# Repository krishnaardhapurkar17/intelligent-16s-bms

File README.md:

# Simulation-First 16S Intelligent BMS

A simulation-first 16-series-cell Intelligent Battery Management System.

## Development Stack
- Python
- PyBaMM
- NumPy / SciPy
- Pandas
- Matplotlib
- Pytest
- KiCad

## Project Scope
- 16S battery modelling
- Cell monitoring
- SOC/SOH/SOP/SOS estimation
- Fault detection and localization
- Active balancing simulation
- AI-based battery diagnostics
- CMU/BMU/PMU/BDU architecture
- Verification and validation

## Project Status
Simulation models, diagnostics, supervisory controls, PMU/IMU/TMU abstractions,
and BDU protection logic are present. Transport-independent message contracts,
simulation command authorization, and lifecycle event logging/replay are also
implemented. See `docs/requirements-traceability-matrix.md` for verified gaps;
the RTM is an engineering worklist, not a certification statement.
The [75-task evidence-based tracker reconciliation](outputs/01a1c0ed-8d57-7813-b837-d1bb78c2df39/project_tracker_reconciliation.xlsx)
is the detailed cross-project status view. The two supplied project-tracker
workbooks also now contain current status/evidence fields; their original task
statuses are retained in a baseline column. The GOV-003 workbook preserves its
original audit sheets and includes a dated current-scope addendum. The V&V,
execution, and risk Word plans have dated status addenda; their original
baseline content remains in place.

The hardware files are a non-release schematic/design study. Grounded USB
service is prohibited while the pack is connected; the active-balancer is
deferred from the build/procurement baseline; external high-voltage switching
components remain unselected; and physical IMD/HVIL, PCB layout and physical
validation are outside the current scope. Do not connect a battery to the
draft design.

Reproducible idealized precharge R-C, software fault-injection, and synthetic dynamic-load SOC
initialization experiments are included. They are software-model evidence,
not KiCad SPICE, component-model, hardware, or vehicle validation. See
`docs/portfolio-evidence-register.md`.

## Supplied AI estimators

Supplied NMC/NMC-LCO model assets are preserved under `models/ai/`. Portable
LFP SOH/RUL forests trained on UConn reference performance tests are also
available through the AI adapter; their whole-cell held-out results and limits
are documented in `models/ai/README.md`. LFP SOC AI remains disabled because
the available data do not support independent cell-held-out validation of a
temperature-aware model. All AI estimates are research-only warnings and must
not replace primary protection logic. See `models/ai/README.md` for feature
contracts and verification evidence.

## Run checks
Create an isolated environment and install the core project dependencies:

```powershell
py -m venv .venv
.\.venv\Scripts\python.exe -m pip install -r environment/requirements-core.txt
```

For SOC CNN-LSTM inference, also install
`.\.venv\Scripts\python.exe -m pip install -r environment/requirements-ai.txt`.
Run the regression suite with
`.\.venv\Scripts\python.exe tests/regression/run_regression.py`. It writes its
report under `results/regression/`.

Regenerate the focused assumption-only experiments with:

```powershell
.\.venv\Scripts\python.exe tools\run_precharge_assumption_sim.py
.\.venv\Scripts\python.exe tools\run_soc_drive_cycle_experiment.py
.\.venv\Scripts\python.exe tools\run_software_fault_injection_report.py
```

## LFP model data workflow

Keep the downloaded raw files in `datasets/` (they are excluded from Git). Run
`.\.venv\Scripts\python.exe tools/prepare_lfp_dataset.py --all` to build compact
tables under `results/raw/lfp/`, then run
`.\.venv\Scripts\python.exe tools/train_lfp_tree_models.py` to train LFP SOH/RUL
forests and reproduce the whole-cell validation report. Add
`--split protocol-group` to evaluate on unseen aging conditions. See
`models/ai/README.md` for metrics, limits, and the disabled LFP SOC AI path.

For the complete unit suite, run
`.\.venv\Scripts\python.exe -m pytest tests/unit -q`. For statement and
branch coverage, install `environment/requirements-dev.txt`, run
`coverage run --branch --source=software,models -m pytest tests/unit -q`, then
`coverage report -m`. The current result is recorded in
`results/metrics/unit_test_coverage.json`; coverage is not a safety metric.

## Limitations
Simulation and engineering design project.
Not safety certified or production qualified.

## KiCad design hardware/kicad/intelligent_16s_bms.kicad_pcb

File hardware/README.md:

# Hardware workspace

The hardware design is a control-board schematic draft. Pack current remains
off-board through external contactors, fuse, shunt and precharge components.
No board is being fabricated or physically tested.

## Integrated CAD

- [Integrated KiCad schematic](kicad/intelligent_16s_bms.kicad_sch)
- [Integrated schematic PDF](schematic-pdf/intelligent_16s_bms_system.pdf)
- [Integrated ERC report](kicad/integrated_erc.txt)
- [Integrated netlist](kicad/intelligent_16s_bms.net)
- [Draft BOM](bom/intelligent_16s_bms_draft.csv)
- [BOM authority and status](bom/README.md)
- [Design checklist](requirements-status.md)
- [Circuit definition and release gates](circuit-definition.md)

The source-page generators are in `tools/generate_afe_schematic.py`,
`tools/generate_controller_schematic.py`, `tools/generate_power_schematic.py`
and `tools/generate_balancer_schematic.py`. Recreate the project entry sheet
with `tools/merge_hardware_schematic.py` after regenerating the child sheets.
The root schematic is intentionally a single project sheet with separate child
sheets for AFE, controller, power/auxiliary logic and active balancing, instead
of one giant flat capture. The root plus four child sheets make a five-page
project. The sheets use global labels for cross-sheet nets and distinct
reference ranges for the controller, auxiliary-power and active-balancer pages.

From the repository root, regenerate the design and project-local symbol
library with:

```powershell
python .\tools\generate_afe_schematic.py
python .\tools\generate_controller_schematic.py
python .\tools\generate_power_schematic.py
python .\tools\generate_balancer_schematic.py
python .\tools\merge_hardware_schematic.py
python .\tools\export_kicad_custom_library.py
```

KiCad 10.0.6 ERC on the top-level, five-page schematic reports zero errors and
zero warnings with `--severity-all`. The report lists excluded check classes,
including SPICE-model issues. ERC checks schematic rules only; it is not
electrical design approval, circuit simulation, or DRC.

The controller and active-balancer source sheets now include explicit review
warnings. These are annotation-only changes; no connectivity was changed. The
schematic PDF and ERC report are refreshed from the integrated schematic.

## Current scope decisions

- Grounded USB service is prohibited while the pack is connected; no live-pack
  USB isolation redesign is claimed.
- The active-balancer circuit is a study only and is deferred from the
  build/procurement baseline. Do not populate or procure its transformer
  candidate without approval or a reviewed replacement.
- External pack switching, fuse, shunt and precharge hardware remain
  unselected. The physical IMD/HVIL, PCB layout, KiCad SPICE simulation,
  fabrication and all physical testing are outside this revision.
- The package is not a hardware release. Do not connect a battery to this
  unvalidated draft.

The KiCad PCB file contains imported footprints but no routed copper, vias,
zones or DRC evidence. It is an unrouted placement draft, not a completed
layout. Contactor coil settings remain provisional; cell-specific
configuration, external contactor/fuse/precharge selection, physical IMD/HVIL
and independent review remain open if hardware release is later pursued.

The idealized software precharge study is reproducible with
`tools/run_precharge_assumption_sim.py`; it is not a KiCad SPICE run or
component-model validation. KiCad circuit-level simulation remains open and is
intentionally untouched in this revision.

The software state-machine behavior is described in
`docs/bdu-state-machine.md`; project status and limitations are summarized in
`docs/portfolio-evidence-register.md`.

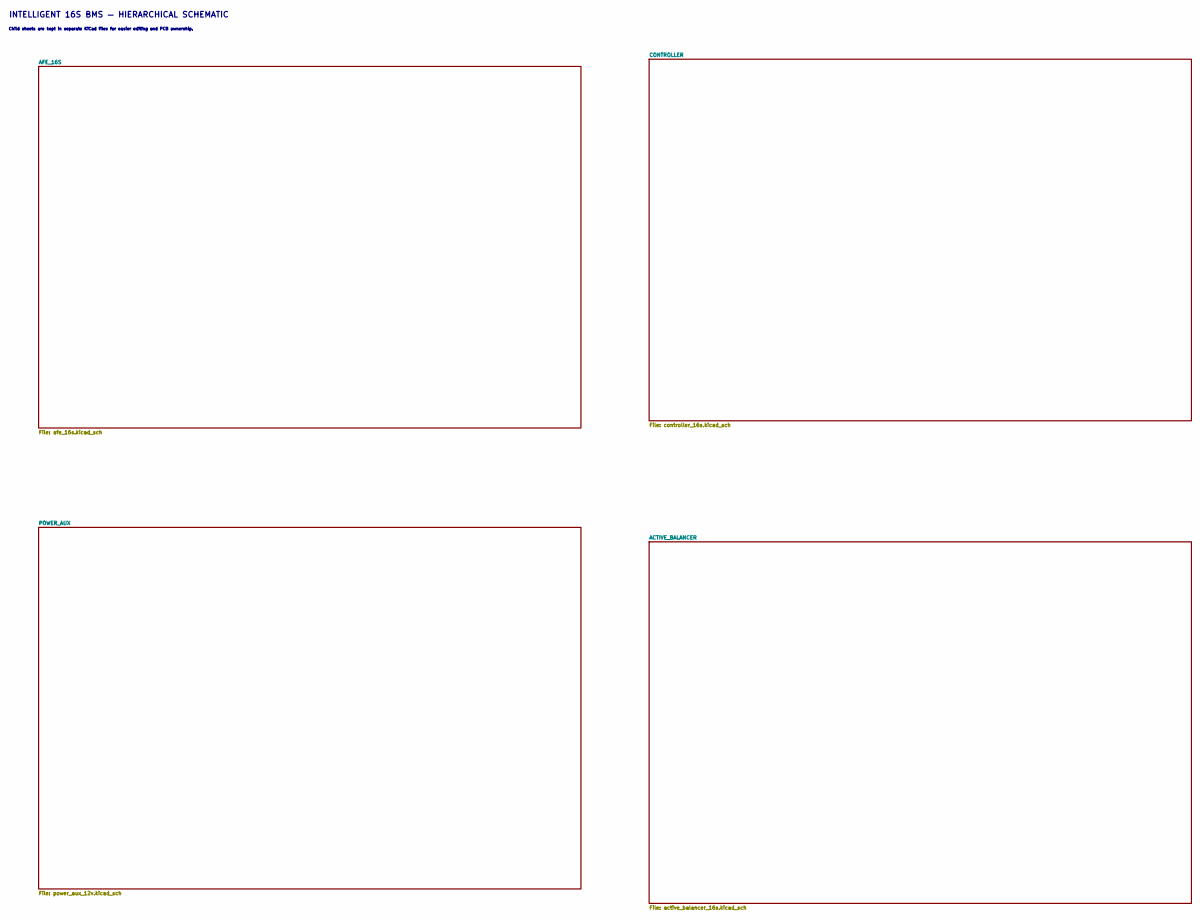
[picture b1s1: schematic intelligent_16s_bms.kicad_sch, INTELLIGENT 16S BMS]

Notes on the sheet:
Child sheets are kept in separate KiCad files for easier editing and PCB ownership.
INTELLIGENT 16S BMS — HIERARCHICAL SCHEMATIC

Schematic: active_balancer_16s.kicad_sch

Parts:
C301, C302, C303, C304, C305, C306, C307, C308, C309, C310, C311, C312, C313, C314, C315, C316: 47uF 16V X7R; Ceff >= 12uF; C_1210_3225Metric
C320, C321, C322: 10uF VREG bulk; C_0805_2012Metric
C330, C332, C334: 100nF isolator bypass; C_0603_1608Metric
C331, C333, C335: 100nF local isolator bypass; C_0603_1608Metric
C336: 100nF boost capacitor; C_0603_1608Metric
D30: Schottky; VRRM>6V, surge>=1A; D_SOD-123
J30: BALANCE POWER TAPS VC0..VC16; 3 spare; Molex_Mini-Fit_Jr_5566-20A_2x10_P4.20mm_Vertical
Q30, Q31, Q32, Q33, Q34, Q35, Q36, Q37, Q38, Q39, Q40, Q41, Q42, Q43, Q44, Q45, Q46, Q47, Q48, Q49, Q50, Q51, Q52, Q53, Q54, Q55, Q56, Q57, Q58, Q59, Q60, Q61: BUK9Y22-100E 100V; LFPAK56
Q62, Q63, Q64: BC857B-Q WDT pause; SOT-23
R301, R303, R305, R307, R309, R311, R313, R315, R317, R319, R321, R323, R325, R327, R329, R331: 25mR 1% primary peak sense; R_2512_6332Metric
R302, R304, R306, R308, R310, R312, R314, R316, R318, R320, R322, R324, R326, R328, R330, R332: 25mR 1% secondary peak sense; R_2512_6332Metric
R340, R342, R344: 20k RTONP; R_0603_1608Metric
R341, R343, R345: 15k RTONS; R_0603_1608Metric
R349: 6.8R boost inrush; R_0603_1608Metric
R350, R351, R352: 10k WDT pull-up; R_0603_1608Metric
R353, R354, R355: 10k SDO pull-up; R_0603_1608Metric
R356, R358, R360: 10k WDT pause drive; R_0603_1608Metric
R357, R359, R361: 100k default inhibit; R_0603_1608Metric
T30, T31, T32, T33, T34, T35, T36, T37, T38, T39, T40, T41, T42, T43, T44, T45: WE-FLYLT 750312504
U30, U31, U32: LTC3300ILXE-2#WPBF; LQFP-48-1EP_7x7mm_P0.5mm_EP3.6x3.6mm
U33, U34, U35: ISO7762F-Q1; SOIC-16W_7.5x10.3mm_P1.27mm

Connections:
3V3: C330.1, C332.1, C334.1, U33.1 (VCC1), U34.1 (VCC1), U35.1 (VCC1); also elsewhere on the board
BAL_BOOST_DIODE_IN: D30.2 (A), R349.1
BAL_BOOST_MINUS_U32: C336.2, U32.41 (BOOST-)
BAL_BOOST_PLUS_U32: C336.1, D30.1 (K), U32.40 (BOOST+)
BAL_CS30: U33.2 (INA); also elsewhere on the board
BAL_CS31: U34.2 (INA); also elsewhere on the board
BAL_CS32: U35.2 (INA); also elsewhere on the board
BAL_CS_LOCAL_U30: U30.16 (CSBI), U33.15 (OUTA)
BAL_CS_LOCAL_U31: U31.16 (CSBI), U34.15 (OUTA)
BAL_CS_LOCAL_U32: U32.16 (CSBI), U35.15 (OUTA)
BAL_G1P_U30: Q30.1 (G), U30.23 (G1P)
BAL_G1P_U31: Q42.1 (G), U31.23 (G1P)
BAL_G1S_U30: Q31.1 (G), U30.11 (G1S)
BAL_G1S_U31: Q43.1 (G), U31.11 (G1S)
BAL_G2P_U30: Q32.1 (G), U30.26 (G2P)
BAL_G2P_U31: Q44.1 (G), U31.26 (G2P)
BAL_G2S_U30: Q33.1 (G), U30.9 (G2S)
BAL_G2S_U31: Q45.1 (G), U31.9 (G2S)
BAL_G3P_U30: Q34.1 (G), U30.29 (G3P)
BAL_G3P_U31: Q46.1 (G), U31.29 (G3P)
BAL_G3P_U32: Q54.1 (G), U32.29 (G3P)
BAL_G3S_U30: Q35.1 (G), U30.7 (G3S)
BAL_G3S_U31: Q47.1 (G), U31.7 (G3S)
BAL_G3S_U32: Q55.1 (G), U32.7 (G3S)
BAL_G4P_U30: Q36.1 (G), U30.32 (G4P)
BAL_G4P_U31: Q48.1 (G), U31.32 (G4P)
BAL_G4P_U32: Q56.1 (G), U32.32 (G4P)
BAL_G4S_U30: Q37.1 (G), U30.5 (G4S)
BAL_G4S_U31: Q49.1 (G), U31.5 (G4S)
BAL_G4S_U32: Q57.1 (G), U32.5 (G4S)
BAL_G5P_U30: Q38.1 (G), U30.35 (G5P)
BAL_G5P_U31: Q50.1 (G), U31.35 (G5P)
BAL_G5P_U32: Q58.1 (G), U32.35 (G5P)
BAL_G5S_U30: Q39.1 (G), U30.3 (G5S)
BAL_G5S_U31: Q51.1 (G), U31.3 (G5S)
BAL_G5S_U32: Q59.1 (G), U32.3 (G5S)
BAL_G6P_U30: Q40.1 (G), U30.38 (G6P)
BAL_G6P_U31: Q52.1 (G), U31.38 (G6P)
BAL_G6P_U32: Q60.1 (G), U32.38 (G6P)
BAL_G6S_U30: Q41.1 (G), U30.1 (G6S)
BAL_G6S_U31: Q53.1 (G), U31.1 (G6S)
BAL_G6S_U32: Q61.1 (G), U32.1 (G6S)
BAL_MOSI: U33.4 (INC), U34.4 (INC), U35.4 (INC); also elsewhere on the board
BAL_MOSI_LOCAL_U30: U30.18 (SDI), U33.13 (OUTC)
BAL_MOSI_LOCAL_U31: U31.18 (SDI), U34.13 (OUTC)
BAL_MOSI_LOCAL_U32: U32.18 (SDI), U35.13 (OUTC)
BAL_PAUSE_BASE_U30: Q62.1 (B), R356.1, R357.2
BAL_PAUSE_BASE_U31: Q63.1 (B), R358.1, R359.2
BAL_PAUSE_BASE_U32: Q64.1 (B), R360.1, R361.2
BAL_PERMIT_LOCAL_U30: R356.2, U33.12 (OUTD)
BAL_PERMIT_LOCAL_U31: R358.2, U34.12 (OUTD)
BAL_PERMIT_LOCAL_U32: R360.2, U35.12 (OUTD)
BAL_PIS_1: Q30.2 (S), R301.2, U30.22 (I1P)
BAL_PIS_2: Q32.2 (S), R303.2, U30.25 (I2P)
BAL_PIS_3: Q34.2 (S), R305.2, U30.28 (I3P)
BAL_PIS_4: Q36.2 (S), R307.2, U30.31 (I4P)
BAL_PIS_5: Q38.2 (S), R309.2, U30.34 (I5P)
BAL_PIS_6: Q40.2 (S), R311.2, U30.37 (I6P)
BAL_PIS_7: Q42.2 (S), R313.2, U31.22 (I1P)
BAL_PIS_8: Q44.2 (S), R315.2, U31.25 (I2P)
BAL_PIS_9: Q46.2 (S), R317.2, U31.28 (I3P)
BAL_PIS_10: Q48.2 (S), R319.2, U31.31 (I4P)
BAL_PIS_11: Q50.2 (S), R321.2, U31.34 (I5P)
BAL_PIS_12: Q52.2 (S), R323.2, U31.37 (I6P)
BAL_PIS_13: Q54.2 (S), R325.2, U32.28 (I3P)
BAL_PIS_14: Q56.2 (S), R327.2, U32.31 (I4P)
BAL_PIS_15: Q58.2 (S), R329.2, U32.34 (I5P)
BAL_PIS_16: Q60.2 (S), R331.2, U32.37 (I6P)
BAL_PSW_1: Q30.3 (D), T30.4 (N1_B), T30.5 (N1_B)
BAL_PSW_2: Q32.3 (D), T31.4 (N1_B), T31.5 (N1_B)
BAL_PSW_3: Q34.3 (D), T32.4 (N1_B), T32.5 (N1_B)
BAL_PSW_4: Q36.3 (D), T33.4 (N1_B), T33.5 (N1_B)
BAL_PSW_5: Q38.3 (D), T34.4 (N1_B), T34.5 (N1_B)
BAL_PSW_6: Q40.3 (D), T35.4 (N1_B), T35.5 (N1_B)
BAL_PSW_7: Q42.3 (D), T36.4 (N1_B), T36.5 (N1_B)
BAL_PSW_8: Q44.3 (D), T37.4 (N1_B), T37.5 (N1_B)
BAL_PSW_9: Q46.3 (D), T38.4 (N1_B), T38.5 (N1_B)
BAL_PSW_10: Q48.3 (D), T39.4 (N1_B), T39.5 (N1_B)
BAL_PSW_11: Q50.3 (D), T40.4 (N1_B), T40.5 (N1_B)
BAL_PSW_12: Q52.3 (D), T41.4 (N1_B), T41.5 (N1_B)
BAL_PSW_13: Q54.3 (D), T42.4 (N1_B), T42.5 (N1_B)
BAL_PSW_14: Q56.3 (D), T43.4 (N1_B), T43.5 (N1_B)
BAL_PSW_15: Q58.3 (D), T44.4 (N1_B), T44.5 (N1_B)
BAL_PSW_16: Q60.3 (D), T45.4 (N1_B), T45.5 (N1_B)
BAL_RTONP_U30: R340.2, U30.14 (RTONP)
BAL_RTONP_U31: R342.2, U31.14 (RTONP)
BAL_RTONP_U32: R344.2, U32.14 (RTONP)
BAL_RTONS_U30: R341.2, U30.13 (RTONS)
BAL_RTONS_U31: R343.2, U31.13 (RTONS)
BAL_RTONS_U32: R345.2, U32.13 (RTONS)
BAL_SCK: U33.3 (INB), U34.3 (INB), U35.3 (INB); also elsewhere on the board
BAL_SCK_LOCAL_U30: U30.17 (SCKI), U33.14 (OUTB)
BAL_SCK_LOCAL_U31: U31.17 (SCKI), U34.14 (OUTB)
BAL_SCK_LOCAL_U32: U32.17 (SCKI), U35.14 (OUTB)
BAL_SDO30: U33.6 (OUTE); also elsewhere on the board
BAL_SDO31: U34.6 (OUTE); also elsewhere on the board
BAL_SDO32: U35.6 (OUTE); also elsewhere on the board
BAL_SDO_LOCAL_U33: R353.1, U30.19 (SDO), U33.11 (INE)
BAL_SDO_LOCAL_U34: R354.1, U31.19 (SDO), U34.11 (INE)
BAL_SDO_LOCAL_U35: R355.1, U32.19 (SDO), U35.11 (INE)
BAL_SIS_1: Q31.2 (S), R302.2, U30.12 (I1S)
BAL_SIS_2: Q33.2 (S), R304.2, U30.10 (I2S)
BAL_SIS_3: Q35.2 (S), R306.2, U30.8 (I3S)
BAL_SIS_4: Q37.2 (S), R308.2, U30.6 (I4S)
BAL_SIS_5: Q39.2 (S), R310.2, U30.4 (I5S)
BAL_SIS_6: Q41.2 (S), R312.2, U30.2 (I6S)
BAL_SIS_7: Q43.2 (S), R314.2, U31.12 (I1S)
BAL_SIS_8: Q45.2 (S), R316.2, U31.10 (I2S)
BAL_SIS_9: Q47.2 (S), R318.2, U31.8 (I3S)
BAL_SIS_10: Q49.2 (S), R320.2, U31.6 (I4S)
BAL_SIS_11: Q51.2 (S), R322.2, U31.4 (I5S)
BAL_SIS_12: Q53.2 (S), R324.2, U31.2 (I6S)
BAL_SIS_13: Q55.2 (S), R326.2, U32.8 (I3S)
BAL_SIS_14: Q57.2 (S), R328.2, U32.6 (I4S)
BAL_SIS_15: Q59.2 (S), R330.2, U32.4 (I5S)
BAL_SIS_16: Q61.2 (S), R332.2, U32.2 (I6S)
BAL_SSW_1: Q31.3 (D), T30.9 (N2_B), T30.10 (N2_B)
BAL_SSW_2: Q33.3 (D), T31.9 (N2_B), T31.10 (N2_B)
BAL_SSW_3: Q35.3 (D), T32.9 (N2_B), T32.10 (N2_B)
BAL_SSW_4: Q37.3 (D), T33.9 (N2_B), T33.10 (N2_B)
BAL_SSW_5: Q39.3 (D), T34.9 (N2_B), T34.10 (N2_B)
BAL_SSW_6: Q41.3 (D), T35.9 (N2_B), T35.10 (N2_B)
BAL_SSW_7: Q43.3 (D), T36.9 (N2_B), T36.10 (N2_B)
BAL_SSW_8: Q45.3 (D), T37.9 (N2_B), T37.10 (N2_B)
BAL_SSW_9: Q47.3 (D), T38.9 (N2_B), T38.10 (N2_B)
BAL_SSW_10: Q49.3 (D), T39.9 (N2_B), T39.10 (N2_B)
BAL_SSW_11: Q51.3 (D), T40.9 (N2_B), T40.10 (N2_B)
BAL_SSW_12: Q53.3 (D), T41.9 (N2_B), T41.10 (N2_B)
BAL_SSW_13: Q55.3 (D), T42.9 (N2_B), T42.10 (N2_B)
BAL_SSW_14: Q57.3 (D), T43.9 (N2_B), T43.10 (N2_B)
BAL_SSW_15: Q59.3 (D), T44.9 (N2_B), T44.10 (N2_B)
BAL_SSW_16: Q61.3 (D), T45.9 (N2_B), T45.10 (N2_B)
BAL_TAP0: C301.2, C320.2, C331.2, J30.1, R301.1, R302.1, R304.1, R306.1, R308.1, R310.1, R312.1, R340.1, R341.1, U30.15 (CTRL), U30.21 (V-), U30.42 (BOOST), U30.43 (A0), U30.44 (A1), U30.45 (A2), U30.46 (A3), U30.47 (A4), U30.49 (EPAD_V-), U33.9 (GND2)
BAL_TAP1: C301.1, C302.2, J30.2, R303.1, T30.1 (N1_A), T30.2 (N1_A), U30.24 (C1)
BAL_TAP2: C302.1, C303.2, J30.3, R305.1, T31.1 (N1_A), T31.2 (N1_A), U30.27 (C2)
BAL_TAP3: C303.1, C304.2, J30.4, R307.1, T32.1 (N1_A), T32.2 (N1_A), U30.30 (C3)
BAL_TAP4: C304.1, C305.2, J30.5, R309.1, T33.1 (N1_A), T33.2 (N1_A), U30.33 (C4)
BAL_TAP5: C305.1, C306.2, J30.6, R311.1, T34.1 (N1_A), T34.2 (N1_A), U30.36 (C5)
BAL_TAP6: C306.1, C307.2, C321.2, C333.2, J30.7, R313.1, R314.1, R316.1, R318.1, R320.1, R322.1, R324.1, R342.1, R343.1, T35.1 (N1_A), T35.2 (N1_A), U30.39 (C6), U31.15 (CTRL), U31.21 (V-), U31.42 (BOOST), U31.44 (A1), U31.45 (A2), U31.46 (A3), U31.47 (A4), U31.49 (EPAD_V-), U34.9 (GND2)
BAL_TAP7: C307.1, C308.2, J30.8, R315.1, T36.1 (N1_A), T36.2 (N1_A), U30.40 (BOOST+), U31.24 (C1)
BAL_TAP8: C308.1, C309.2, J30.9, R317.1, T37.1 (N1_A), T37.2 (N1_A), U31.27 (C2)
BAL_TAP9: C309.1, C310.2, J30.10, R319.1, T38.1 (N1_A), T38.2 (N1_A), U31.30 (C3)
BAL_TAP10: C310.1, C311.2, J30.11, R321.1, T39.1 (N1_A), T39.2 (N1_A), U31.33 (C4)
BAL_TAP11: C311.1, C312.2, J30.12, R323.1, T40.1 (N1_A), T40.2 (N1_A), U31.36 (C5)
BAL_TAP12: C312.1, C313.2, C322.2, C335.2, J30.13, R325.1, R326.1, R328.1, R330.1, R332.1, R344.1, R345.1, T30.6 (N2_A), T30.7 (N2_A), T31.6 (N2_A), T31.7 (N2_A), T32.6 (N2_A), T32.7 (N2_A), T33.6 (N2_A), T33.7 (N2_A), T34.6 (N2_A), T34.7 (N2_A), T35.6 (N2_A), T35.7 (N2_A), T41.1 (N1_A), T41.2 (N1_A), U31.39 (C6), U32.15 (CTRL), U32.21 (V-), U32.24 (C1), U32.27 (C2), U32.43 (A0), U32.45 (A2), U32.46 (A3), U32.47 (A4), U32.49 (EPAD_V-), U35.9 (GND2)
BAL_TAP13: C313.1, C314.2, J30.14, R327.1, T42.1 (N1_A), T42.2 (N1_A), U31.40 (BOOST+), U32.30 (C3)
BAL_TAP14: C314.1, C315.2, J30.15, R329.1, T43.1 (N1_A), T43.2 (N1_A), U32.33 (C4)
BAL_TAP15: C315.1, C316.2, J30.16, R331.1, T44.1 (N1_A), T44.2 (N1_A), U32.36 (C5)
BAL_TAP16: C316.1, J30.17, R349.2, T36.6 (N2_A), T36.7 (N2_A), T37.6 (N2_A), T37.7 (N2_A), T38.6 (N2_A), T38.7 (N2_A), T39.6 (N2_A), T39.7 (N2_A), T40.6 (N2_A), T40.7 (N2_A), T41.6 (N2_A), T41.7 (N2_A), T42.6 (N2_A), T42.7 (N2_A), T43.6 (N2_A), T43.7 (N2_A), T44.6 (N2_A), T44.7 (N2_A), T45.1 (N1_A), T45.2 (N1_A), T45.6 (N2_A), T45.7 (N2_A), U32.39 (C6)
BAL_VREG_U30: C320.1, C331.1, Q62.3 (E), R350.2, R353.2, R357.1, U30.48 (VREG), U33.16 (VCC2)
BAL_VREG_U31: C321.1, C333.1, Q63.3 (E), R351.2, R354.2, R359.1, U31.43 (A0), U31.48 (VREG), U34.16 (VCC2)
BAL_VREG_U32: C322.1, C335.1, Q64.3 (E), R352.2, R355.2, R361.1, U32.42 (BOOST), U32.44 (A1), U32.48 (VREG), U35.16 (VCC2)
BAL_WDT30: U33.7 (OUTF); also elsewhere on the board
BAL_WDT31: U34.7 (OUTF); also elsewhere on the board
BAL_WDT32: U35.7 (OUTF); also elsewhere on the board
BAL_WDT_LOCAL_U33: Q62.2 (C), R350.1, U30.20 (WDT), U33.10 (INF)
BAL_WDT_LOCAL_U34: Q63.2 (C), R351.1, U31.20 (WDT), U34.10 (INF)
BAL_WDT_LOCAL_U35: Q64.2 (C), R352.1, U32.20 (WDT), U35.10 (INF)
BMS_PERMIT: U33.5 (IND), U34.5 (IND), U35.5 (IND); also elsewhere on the board
GND: C330.2, C332.2, C334.2, U33.8 (GND1), U34.8 (GND1), U35.8 (GND1); also elsewhere on the board

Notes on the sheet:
Top U32 uses BOOST=VREG and the datasheet Schottky/flying-capacitor circuit; U30/U31 use the next higher cell rail.
Cell 16 / U32 channel 6
Only one cell channel stack-wide at a time in firmware. Charge-only policy; require closed BDU, valid sensors, no fault, and all cell temperatures <45C.
Harness ampacity, individual tap fusing, mating contacts and connector thermal derating are open release items.
WE 750312504 pairs: 1+2, 4+5, 6+7, 9+10 are common terminals. Not automotive-qualified; confirm permitted use and replace/approve before release.
Separate high-current J30 harness: pins 1-17 = BAL_TAP0..16, pins 18-20 spare. Connect taps at the cell stack; keep balance current out of the AFE sense harness/filter.
U30 address BAL_TAP0BAL_TAP0BAL_TAP0BAL_TAP0BAL_TAP0 (A4..A0); secondary span BAL_TAP0..BAL_TAP12
Cell 8 / U31 channel 2
U32 address BAL_TAP12BAL_TAP12BAL_TAP12BAL_VREG_U32BAL_TAP12 (A4..A0); secondary span BAL_TAP12..BAL_TAP16
Cell 11 / U31 channel 5
U30: CTRL=V- multi-transformer mode; address 0.
Cell 4 / U30 channel 4
U32: CTRL=V- multi-transformer mode; address 2.
Cell 1 / U30 channel 1
16S TRANSFORMER-COUPLED ACTIVE BALANCER — ENGINEERING DRAFT
Cell 13 / U32 channel 3
Cell 7 / U31 channel 1
Cell 15 / U32 channel 5
Cell bypass capacitors require >=12uF effective per cell at bias/temperature for the 1A broken-connection design target; 47uF nominal is provisional.
Cell 10 / U31 channel 4
Cell 9 / U31 channel 3
25mR sense gives 2A peak. With 1:1 turns and S=4..12, first-order cell transfer is below 1A; tune/verify with actual magnetics.
Cell 2 / U30 channel 2
Cell 6 / U30 channel 6
16 channels: U30 cells 1-6 / 12S secondary; U31 cells 7-12 / 10S secondary; U32 cells 13-16 / 4S secondary.
Cell 12 / U31 channel 6
Cell 5 / U30 channel 5
U35: default-low isolation; BMS_PERMIT low drives BAL_PERMIT_LOCAL_U32 low and forces LTC WDT high.
U31 address BAL_TAP6BAL_TAP6BAL_TAP6BAL_TAP6BAL_VREG_U31 (A4..A0); secondary span BAL_TAP6..BAL_TAP16
Cell 14 / U32 channel 4
Not a fabrication release. LTC3300-2 Rev. B application topology adapted to 16S; no PCB/physical validation.
U33: default-low isolation; BMS_PERMIT low drives BAL_PERMIT_LOCAL_U30 low and forces LTC WDT high.
Primary/secondary snubbers (ADI starting point: 330R + 100pF in series per winding) are not populated; determine by ringing/thermal analysis.
U31: CTRL=V- multi-transformer mode; address 1.
U34: default-low isolation; BMS_PERMIT low drives BAL_PERMIT_LOCAL_U31 low and forces LTC WDT high.
Cell 3 / U30 channel 3

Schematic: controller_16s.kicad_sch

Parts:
C101: 100nF; C_0603_1608Metric
C102: 10uF; C_0805_2012Metric
C103: 10nF ADC filter; C_0603_1608Metric
C104: 100nF board NTC filter; C_0603_1608Metric
C105, C106, C107: 0.62uF latch-off delay; C_0805_2012Metric
C108: 10uF coil rail bulk; C_1206_3216Metric
C109: 100nF CRST delay; C_0603_1608Metric
C110: 100nF supervisor delay; C_0603_1608Metric
C111: 15nF VINP bypass; C_0402_1005Metric
C112: 10uF VINP bulk; C_0805_2012Metric
C113: 15nF VCC bypass; C_0402_1005Metric
C114: 22uF isolated output bulk; C_1206_3216Metric
C116: 1nF shield HF bond 2kV; C_1206_3216Metric
C117: 1uF 5V_AUX local bypass; C_0805_2012Metric
D4: ESD2CAN24DCKRQ1; SOT-323_SC-70
D5: TPD1E10B06DYARQ1 VBUS ESD; D_SOD-523
D6: BAT54H-Q upper ADC clamp; D_SOD-123
D7: BAT54H-Q lower ADC clamp; D_SOD-123
D8, D9, D10: BAT54H-Q WDT status OR; D_SOD-123
FLG101, FLG103: PWR_FLAG
J101: 3V3_VSS_IN; PinHeader_1x03_P2.54mm_Vertical
J102: USB_SERVICE; USB_C_Receptacle_Molex_105450-0101
J103: CAN_BUS_SHIELD; TerminalBlock_Phoenix_MKDS-1,5-4-5.08_1x04_P5.08mm_Horizont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
J104: BDU_CONTROL_INTERFACE; PinHeader_1x10_P2.54mm_Vertical
J105: AFE_I2C_ALERT; PinHeader_1x03_P2.54mm_Vertical
J107: BOARD_NTC; PinHeader_1x02_P2.54mm_Vertical
J108: LOAD_SIDE_VOLTAGE_SENSE; TerminalBlock_Phoenix_MKDS-1,5-2-5.08_1x02_P5.08mm_Horizont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
J109: COIL_OUTPUTS; TerminalBlock_Phoenix_MKDS-1,5-4-5.08_1x04_P5.08mm_Horizont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
R101: 10k MCU_EN pullup; R_0603_1608Metric
R102, R103, R104: 100k pulldown; R_0603_1608Metric
R110: 10k IO0 strap pullup; R_0603_1608Metric
R111, R112: 5.1k USB-C Rd; R_0603_1608Metric
R113, R114, R115: 2.2k 12V opto input; R_0805_2012Metric
R116, R117, R118: 10k logic pullup; R_0603_1608Metric
R119, R120: 280k 1% 0805; R_0805_2012Metric
R121: 27k 1%; R_0603_1608Metric
R122: 10k ADC limiter; R_0603_1608Metric
R123: 10k board NTC pullup; R_0603_1608Metric
R124: 120R CAN termination DNP; R_0603_1608Metric
R130: 100k BMS_PERMIT default-off; R_0603_1608Metric
R131, R132, R133: 1k smart-switch current limit 2A; R_0603_1608Metric
R134, R135, R136: 10k driver fault pullup; R_0603_1608Metric
R140: 10k CWD timing select; R_0603_1608Metric
R141: 10k WDO pullup; R_0603_1608Metric
R142: 10k AFE supervisor pullup; R_0603_1608Metric
R143: 10k watchdog rearm default-high; R_0603_1608Metric
R144: 100k WDT status pulldown; R_0603_1608Metric
R150: 22k EN_FLT pullup; R_0603_1608Metric
R151: 1M shield bleed; R_1206_3216Metric
U2: ESP32-S3-WROOM-1-N16R8; ESP32-S3-WROOM-1
U3: ISO1042DWRQ1; SOIC-16W_7.5x10.3mm_P1.27mm
U4, U5, U6: PC817 feedback optocoupler; DIP-4_W7.62mm
U7, U8, U9: TPS1H200A-Q1; Texas_DGN0008D_VSSOP-8-1EP_3x3mm_P0.65mm_EP2x2.94mm_Mask1.5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
U10: SN74LVC1G08-Q1 AFE health gate; SOT-23-5
U11: SN74LVC1G08-Q1 watchdog permit gate; SOT-23-5
U12, U13, U14: SN74LVC1G08-Q1; SOT-23-5
U15: TPS3430WQDRCRQ1; Texas_DRC0010J
U16: TPS3808G18QDBVRQ1; SOT-23-6
U17: UCC33421QDHARQ1
U18: TPD4E02B04-Q1; USON-10_2.5x1.0mm_P0.5mm
U23, U24: SN74LVC1G00-Q1 watchdog fault latch; SOT-23-5
U25: SN74LVC1G08-Q1 startup/watchdog set; SOT-23-5
U26: SN74LVC1G08-Q1 latched watchdog permit; SOT-23-5

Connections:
3V3: C101.1, C102.1, D6.1 (K), FLG101.1, J101.1, R101.2, R110.2, R116.2, R117.2, R118.2, R123.2, R134.2, R135.2, R136.2, R140.2, R141.2, R142.2, R143.2, U2.2 (3V3), U3.1 (VCC1), U7.2 (DIAG_EN), U8.2 (DIAG_EN), U9.2 (DIAG_EN), U10.5 (VCC), U11.5 (VCC), U12.5 (VCC), U13.5 (VCC), U14.5 (VCC), U15.1 (VDD1), U15.10 (VDD2), U16.3 (~MR), U16.6 (VDD), U23.5 (VCC), U24.5 (VCC), U25.5 (VCC), U26.5 (VCC); also elsewhere on the board
5V_AUX: C111.1, C112.1, C117.1, R150.2, U17.2 (VINP); also elsewhere on the board
AFE_OK: U10.4, U11.1
AFE_PG_CT: C110.1, U16.4 (CT)
AFE_PG_OK: R142.1, U10.2, U16.1 (~RESET), U25.2
ALERT_AFE: J105.3, U2.20 (IO12), U10.1; also elsewhere on the board
AUX_12V: C108.1, U7.8 (VS), U8.8 (VS), U9.8 (VS); also elsewhere on the board
BAL_CS30: U2.9 (IO16); also elsewhere on the board
BAL_CS31: U2.23 (IO21); also elsewhere on the board
BAL_CS32: U2.24 (IO47); also elsewhere on the board
BAL_MOSI: U2.8 (IO15); also elsewhere on the board
BAL_SCK: U2.22 (IO14); also elsewhere on the board
BAL_SDO30: U2.31 (IO38); also elsewhere on the board
BAL_SDO31: U2.32 (IO39); also elsewhere on the board
BAL_SDO32: U2.33 (IO40); also elsewhere on the board
BAL_WDT30: D8.2 (A); also elsewhere on the board
BAL_WDT31: D9.2 (A); also elsewhere on the board
BAL_WDT32: D10.2 (A); also elsewhere on the board
BAL_WDT_ANY: D8.1 (K), D9.1 (K), D10.1 (K), R144.2, U2.34 (IO41)
BDU_LOAD_PLUS: J108.1, R119.2
BMS_PERMIT: J104.4, R130.2, U11.4, U12.2, U13.2, U14.2; also elsewhere on the board
BOARD_TEMP_ADC: C104.1, J107.1, R123.1, U2.38 (IO2)
CANH_ISO: D4.2 (CANH), J103.1, R124.2, U3.13 (CANH)
CANL_ISO: D4.1 (CANL), J103.2, R124.1, U3.12 (CANL)
CAN_GND_ISO: C113.2, C114.2, C116.2, D4.3 (GND), FLG103.1, J103.3, R151.1, U3.9 (GND2), U3.10 (GND2), U3.15 (GND2), U17.12 (GNDS)
CAN_RX: U2.11 (IO18), U3.5 (RXD)
CAN_SHIELD: C116.1, J103.4, R151.2
CAN_TX: U2.10 (IO17), U3.3 (TXD)
CL1: R131.2, U7.4 (CL)
CL2: R132.2, U8.4 (CL)
CL3: R133.2, U9.4 (CL)
DC_LINK_ADC: C103.1, D6.2 (A), D7.1 (K), R122.1, U2.39 (IO1)
DELAY1: C105.1, U7.5 (DELAY)
DELAY2: C106.1, U8.5 (DELAY)
DELAY3: C107.1, U9.5 (DELAY)
DIV_LOW: R120.1, R121.2, R122.2
DIV_MID: R119.1, R120.2
FB1_LED: R113.1, U4.1
FB2_LED: R114.1, U5.1
FB3_LED: R115.1, U6.1
GND: C101.2, C102.2, C103.2, C104.2, C105.2, C106.2, C107.2, C108.2, C109.2, C110.2, C111.2, C112.2, C117.2, D5.2 (A2), D7.2 (A), J101.2, J102.A1 (GND), J102.A12 (GND), J102.B1 (GND), J102.B12 (GND), J102.SH (SHIELD), J104.10, J107.2, J108.2, J109.4, R102.1, R103.1, R104.1, R111.1, R112.1, R121.1, R130.1, R131.1, R132.1, R133.1, R144.1, U2.1 (GND), U2.40 (GND), U2.41 (GND), U3.2 (GND1), U3.8 (GND1), U4.2, U4.3, U5.2, U5.3, U6.2, U6.3, U7.6 (GND), U8.6 (GND), U9.6 (GND), U10.3 (GND), U11.3 (GND), U12.3 (GND), U13.3 (GND), U14.3 (GND), U15.3 (SET0), U15.5 (GND), U15.6 (SET1), U15.11 (GND), U16.2 (GND), U17.4 (GNDP), U18.3 (G), U18.8 (G), U23.3 (GND), U24.3 (GND), U25.3 (GND), U26.3 (GND); also elsewhere on the board
IO0_BOOT: R110.1, U2.27 (IO0)
ISO_PWR_FAULT_N: R150.1, U2.15 (IO3), U17.1 (EN_FLT)
MAIN_NEG_COIL_P: J109.2, U8.7 (OUT)
MAIN_NEG_DRIVER_FAULT_N: R135.1, U2.29 (IO36), U8.3 (FAULT)
MAIN_NEG_DRIVE_EN: U8.1 (IN), U13.4
MAIN_NEG_FB: R117.1, U2.19 (IO11), U5.4
MAIN_NEG_FB_12V: J104.6, R114.2
MAIN_NEG_REQ: J104.2, R103.2, U2.5 (IO5), U13.1
MAIN_POS_COIL_P: J109.1, U7.7 (OUT)
MAIN_POS_DRIVER_FAULT_N: R134.1, U2.28 (IO35), U7.3 (FAULT)
MAIN_POS_DRIVE_EN: U7.1 (IN), U12.4
MAIN_POS_FB: R116.1, U2.7 (IO7), U4.4
MAIN_POS_FB_12V: J104.5, R113.2
MAIN_POS_REQ: J104.1, R102.2, U2.4 (IO4), U12.1
MCU_EN: J101.3, R101.1, U2.3 (EN)
PRECHARGE_COIL_P: J109.3, U9.7 (OUT)
PRECHARGE_DRIVER_FAULT_N: R136.1, U2.30 (IO37), U9.3 (FAULT)
PRECHARGE_DRIVE_EN: U9.1 (IN), U14.4
PRECHARGE_FB: R118.1, U2.18 (IO10), U6.4
PRECHARGE_FB_12V: J104.7, R115.2
PRECHARGE_REQ: J104.3, R104.2, U2.6 (IO6), U14.1
REG18: U16.5 (SENSE); also elsewhere on the board
SCL_AFE: J105.2, U2.17 (IO9); also elsewhere on the board
SDA_AFE: J105.1, U2.12 (IO8); also elsewhere on the board
USB_CC1: J102.A5 (CC1), R111.2
USB_CC2: J102.B5 (CC2), R112.2
USB_MCU_D+: U2.14 (USB_D+), U18.4 (IO3)
USB_MCU_D-: U2.13 (USB_D-), U18.5 (IO4)
USB_RAW_D+: J102.A6 (D+), J102.B6 (D+), U18.1 (IO1)
USB_RAW_D-: J102.A7 (D-), J102.B7 (D-), U18.2 (IO2)
USB_VBUS: D5.1 (A1), J102.A4 (VBUS), J102.A9 (VBUS), J102.B4 (VBUS), J102.B9 (VBUS)
VISO_5V: C113.1, C114.1, U3.11 (VCC2), U3.16 (VCC2), U17.9 (SEL), U17.10 (VCC)
WATCHDOG_HEARTBEAT: J104.9, U2.21 (IO13), U15.7 (WDI)
WDT_CRST: C109.1, U15.4 (CRST)
WDT_CWD: R140.1, U15.2 (CWD)
WD_FAULT_LATCH: U23.4, U24.2
WD_OK: R141.1, U15.8 (~WDO), U25.1, U26.1
WD_OK_LATCH: U23.2, U24.4, U26.2
WD_PERMIT: U11.2, U26.4
WD_REARM_N: R143.1, U2.35 (IO42), U24.1
WD_SET_N: U23.1, U25.4

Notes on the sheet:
Configure BQ ALERT active-low to match the permit gate. TPS3808-Q1 monitors BQ REG18.
LTC3300 WDT status is diode-ORed to GPIO41; BMS_PERMIT is isolated to each balancer and forces its local WDT high on a hardware inhibit.
Fit 120R only at a bus endpoint; CAN_SHIELD is a separate enclosure/chassis bond point.
BDU I/O — external 12V contactors; protected smart coil switches and independent permit logic are on this board
CONTACTOR COIL DRIVERS — active-high permit from BQ health supervisor AND automotive window watchdog
AUTOMOTIVE ISOLATED CAN — ISO1042-Q1 plus reinforced isolated 5V supply and CAN ESD protection
On-board BQ fault/watchdog permit gates all coil requests; pack switching remains external.
TPS3430 WDO pulse and startup power fault set a cross-coupled NAND latch. GPIO42 must pulse WD_REARM_N low only after a healthy heartbeat; default is latched-off.
LOCAL CONTROLLER / ISOLATED CAN / CONTACTOR INTERFACE — DRAFT
Coils return to VSS. Driver current limit/latch timing are provisional 2A / 0.2s settings; confirm pull-in current and thermal rise from selected coil datasheets.
3V3 MCU DOMAIN
